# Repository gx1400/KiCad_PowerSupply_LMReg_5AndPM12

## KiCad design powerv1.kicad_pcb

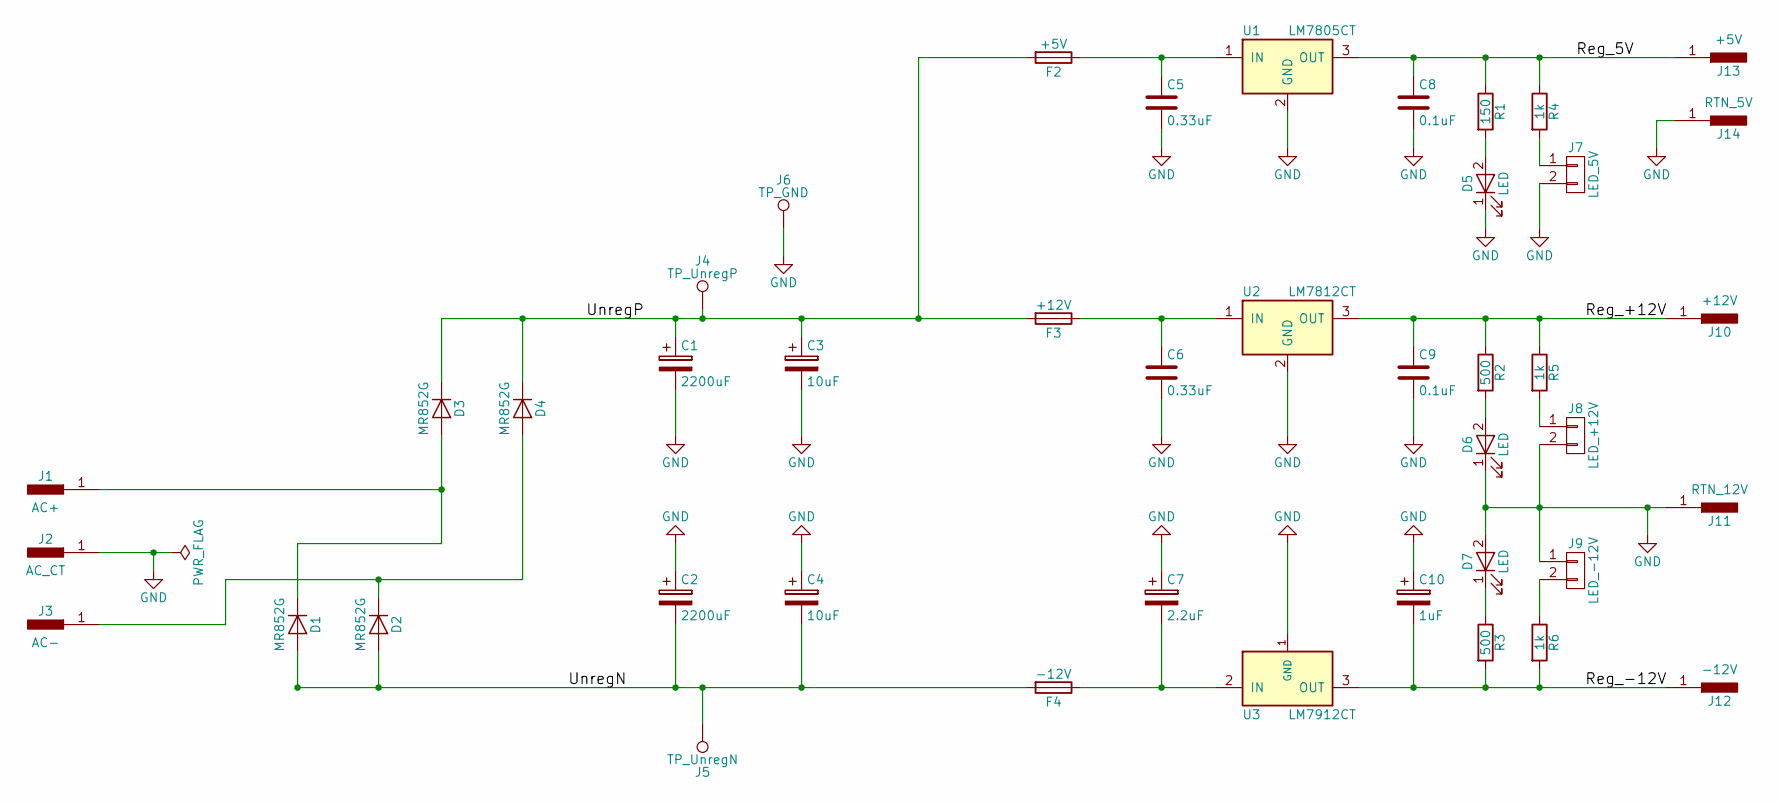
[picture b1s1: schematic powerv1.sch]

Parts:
C1, C2: 2200uF; CP_Radial_D10.0mm_P5.00mm
C3, C4: 10uF; CP_Radial_D10.0mm_P5.00mm
C5, C6: 0.33uF; C_Disc_D7.5mm_W5.0mm_P5.00mm
C7: 2.2uF; CP_Radial_D5.0mm_P2.00mm
C8, C9: 0.1uF; C_Disc_D7.5mm_W5.0mm_P5.00mm
C10: 1uF; CP_Radial_D5.0mm_P2.00mm
D1, D2, D3, D4: MR852G; D_DO-201AD_P15.24mm_Horizontal
D5, D6, D7: LED; LED_0805
F2: +5V; Fuseholder5x20_horiz_open_lateral_Type-II
F3: +12V; Fuseholder5x20_horiz_open_lateral_Type-II
F4: -12V; Fuseholder5x20_horiz_open_lateral_Type-II
J1: AC+; SolderWirePad_2x_1-5mmDrill
J2: AC_CT; SolderWirePad_2x_1-5mmDrill
J3: AC-; SolderWirePad_2x_1-5mmDrill
J4: TP_UnregP; Test_Point_Keystone_5000-5004_Miniature
J5: TP_UnregN; Test_Point_Keystone_5000-5004_Miniature
J6: TP_GND; Test_Point_Keystone_5000-5004_Miniature
J7: LED_5V; Pin_Header_Straight_1x02_Pitch2.54mm
J8: LED_+12V; Pin_Header_Straight_1x02_Pitch2.54mm
J9: LED_-12V; Pin_Header_Straight_1x02_Pitch2.54mm
J10: +12V; SolderWirePad_2x_1-5mmDrill
J11: RTN_12V; SolderWirePad_2x_1-5mmDrill
J12: -12V; SolderWirePad_2x_1-5mmDrill
J13: +5V; SolderWirePad_2x_1-5mmDrill
J14: RTN_5V; SolderWirePad_2x_1-5mmDrill
R1: 150; R_0805_HandSoldering
R2, R3: 500; R_0805_HandSoldering
R4, R5, R6: 1k; R_Axial_DIN0309_L9.0mm_D3.2mm_P5.08mm_Vertical
U1: LM7805CT; TO-220_Vertical
U2: LM7812CT; TO-220_Vertical
U3: LM7912CT; TO-220_Vertical

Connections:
/Reg_5V: C8.1, J13.1, R1.1, R4.1, U1.3 (OUT)
/Reg_+12V: C9.1, J10.1, R2.1, R5.1, U2.3 (OUT)
/Reg_-12V: C10.2, J12.1, R3.2, R6.2, U3.3 (OUT)
/UnregN: C2.2, C4.2, D1.2 (A), D2.2 (A), F4.2, J5.1
/UnregP: C1.1, C3.1, D3.1 (K), D4.1 (K), F2.2, F3.2, J4.1
GND: C1.2, C2.1, C3.2, C4.1, C5.2, C6.2, C7.1, C8.2, C9.2, C10.1, D5.1 (K), D6.1 (K), D7.2 (A), J2.1, J6.1, J7.2, J8.2, J9.1, J11.1, J14.1, U1.2 (GND), U2.2 (GND), U3.1 (GND)
unnamed: C5.1, F2.1, U1.1 (IN)
unnamed: C6.1, F3.1, U2.1 (IN)
unnamed: C7.2, F4.1, U3.2 (IN)
unnamed: D1.1 (K), D3.2 (A), J1.1
unnamed: D2.1 (K), D4.2 (A), J3.1
unnamed: D5.2 (A), R1.2
unnamed: D6.2 (A), R2.2
unnamed: D7.1 (K), R3.1
unnamed: J7.1, R4.2
unnamed: J8.1, R5.2
unnamed: J9.2, R6.1

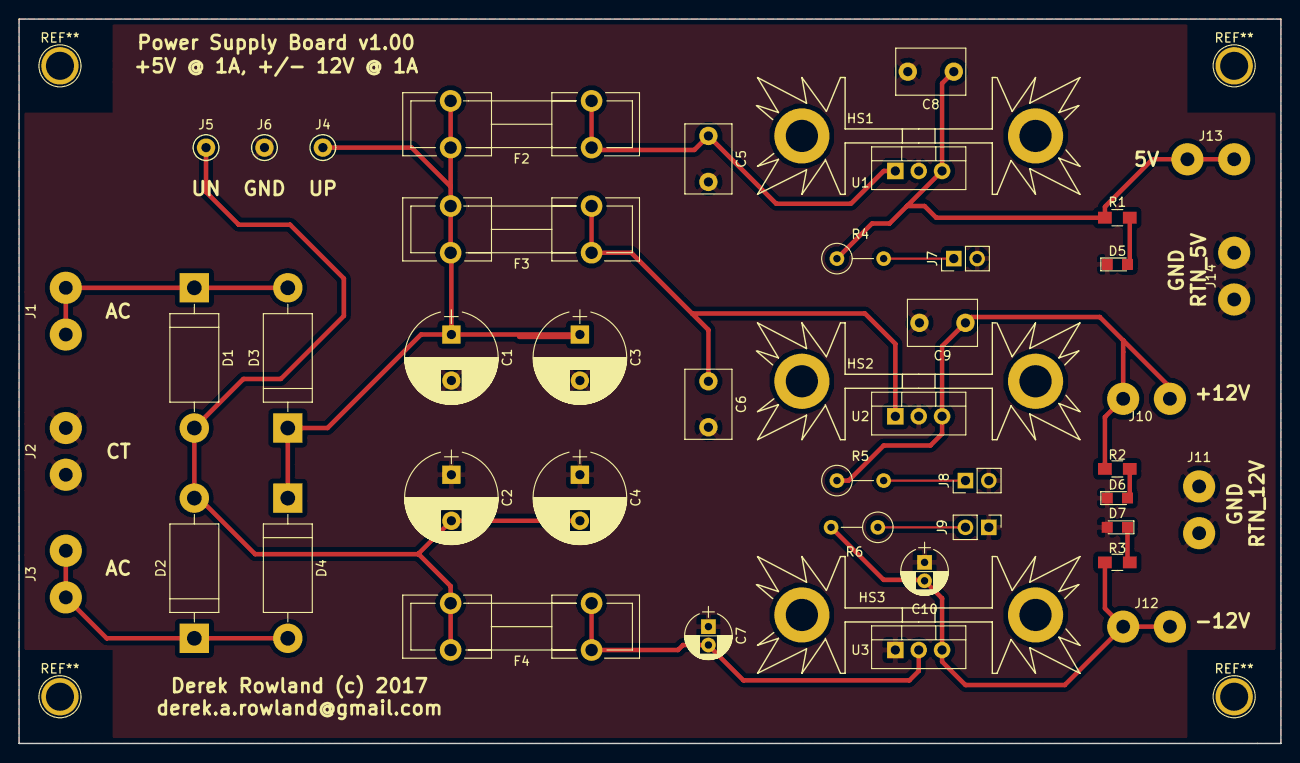
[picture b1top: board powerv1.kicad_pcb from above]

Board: 2 copper layers, 137.2 x 78.7 mm, 46 parts (0 on the bottom side), 17 nets.

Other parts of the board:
HS1, HS2, HS3: Heatsink; Heatsink_Fischer_SK104-STCB_35x13mm__2xDrill3.5mm_ScrewM3

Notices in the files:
powerv1.kicad_pcb:
Derek Rowland (c) 2017
